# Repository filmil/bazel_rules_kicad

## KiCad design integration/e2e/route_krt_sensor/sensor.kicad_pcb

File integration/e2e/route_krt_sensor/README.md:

<!-- SPDX-License-Identifier: Apache-2.0 -->
# The router comparison on hdlf_example_sensor's board

The board of `//e2e/autoroute` is small: three tracks. This package
compares Freerouting and KiCadRoutingTools on a real one: the placed
board of https://github.com/filmil/hdlf_example_sensor (26 footprints, 22
parts and 4 mounting holes; 18 nets; 10 keep-out zones). It has no copper
pours, so KiCadRoutingTools' exact fill, which runs in KiCad's own
Python, is not exercised here either.

The three files are copies of that repository's build outputs, unchanged,
at commit `0a944e6` (main, 2026-11-23):

`:fixtures_test` checks that the copies still have these sha256s.

| File here | Its target there | sha256 |
|---|---|---|
| `sensor.kicad_pcb` | `//pcb:placed_files` (`placed.kicad_pcb`) | `1300850aa979aa9f9b2683427a06a48fdbad86be9aa11f1fa6b892ab01477736` |
| `sensor.kicad_pro` | `//pcb:placed_files` (`placed.kicad_pro`) | `1ca380c225693be96b08735db7b8e454ca0d44a2888a3865b43e9d0d60b547e8` |
| `sensor.net` | `//elec:netlist` (`netlist.net`) | `52ffbad20848262a8f70201be18e84db21b38a26ba245d2aaf50818048122feb` |

Both routers route under the rules the sensor is made to: JLCPCB's
2-layer 1 oz rules from kicad-druid 1.2.0 (MIT,
`//third_party/kicad_druid`), as hdlf_example_sensor uses them. A first
run under this repository's stricter e2e rules (0.25 mm tracks, 0.2 mm
clearance) was no fair comparison: Freerouting left 9 connections
unrouted, and KiCadRoutingTools narrowed 65 of its 242 segments below
0.25 mm. No 3D models are used.

The routing targets are manual, since routing this board takes minutes;
`:placed`, which only stages the board, and `:fixtures_test` are not, so
CI still analyses the package and checks the copies. Run these in
`integration/` (the integration module), on Linux x86_64 (the only host
KiCadRoutingTools' targets support):

```
bazel test //e2e/route_krt_sensor:freerouting_determinism_test //e2e/route_krt_sensor:krt_determinism_test //e2e/route_krt_sensor:krt_board_determinism_test
bazel build //e2e/route_krt_sensor:comparison
```

(A pattern such as `:all` skips manual targets, so they are named.)

Three routers: Freerouting (`freerouting`), KiCadRoutingTools with its
defaults (`krt`), and KiCadRoutingTools with `--escalation board`
(`krt_board`), which narrows a failing net's tracks only down to the
board's own minimums, not the fab's floor.

`comparison.tsv` has one row per router: the DRC's errors and warnings,
the unconnected items, the track length in mm and the vias
(`//krt:compare`). The routing time is not in it, since it differs between
runs; take it from Bazel's execution log (`--execution_log_json_file`,
the `Freerouting` and `KrtRoute` actions). The results are on issue #104.

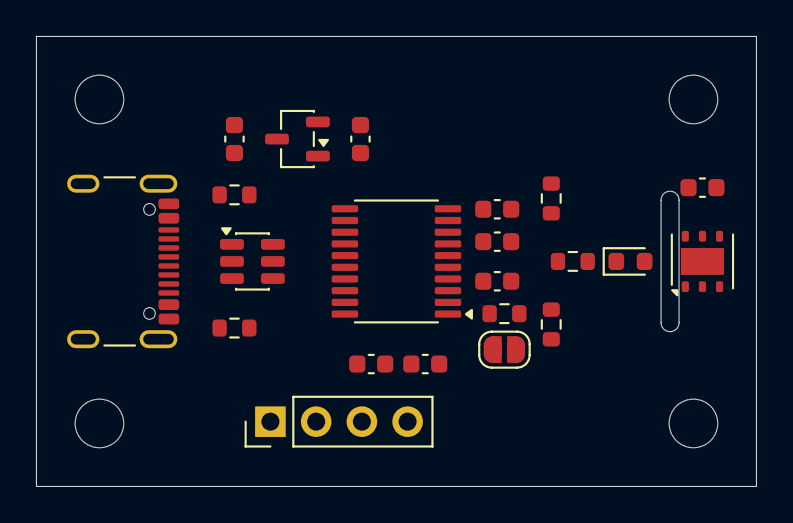
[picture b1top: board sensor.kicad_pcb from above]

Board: 2 copper layers, 40.0 x 25.0 mm, 26 parts (0 on the bottom side), 18 nets, no tracks yet.

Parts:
C1, C2, C6: 1u; C_0603_1608Metric
C3, C7, C8: 100n; C_0603_1608Metric
C4: 4.7u; C_0603_1608Metric
C5: 10n; C_0603_1608Metric
D1: Red; LED_0603_1608Metric
H1, H2, H3, H4: M2.5; MountingHole_2.7mm_M2.5
J1: USB4105-GF-A; USB_C_Receptacle_GCT_USB4105-xx-A_16P_TopMnt_Horizontal
J2: SWD; PinHeader_1x04_P2.54mm_Vertical
JP1: BOOT0; SolderJumper-2_P1.3mm_Open_RoundedPad1.0x1.5mm
R1, R2: 5.1k; R_0603_1608Metric
R3, R4, R5: 10k; R_0603_1608Metric
R6: 1k; R_0603_1608Metric
U1: STM32F042F6P6; TSSOP-20_4.4x6.5mm_P0.65mm
U2: XC6206P332MR; SOT-23-3
U3: HDC2080; Texas_S-PWSON-N6-HDC2080
U4: USBLC6-2SC6; SOT-23-6

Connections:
+3V3: C2.1, C3.1, C4.1, C5.1, C6.1, C8.1, J2.1, JP1.2, R3.2, R4.2, U1.5, U1.16, U2.2, U3.5
BOOT0: JP1.1, R5.1, U1.1
CC1: J1.A5, R1.1
CC2: J1.B5, R2.1
DRDY: U1.6, U3.4
GND: C1.2, C2.2, C3.2, C4.2, C5.2, C6.2, C7.2, C8.2, D1.1, J1.A1, J1.A12, J1.B1, J1.B12, J1.S1, J2.4, R1.2, R2.2, R5.2, U1.15, U2.1, U3.2, U3.3, U4.2
I2C_SCL: R4.1, U1.3, U3.6
I2C_SDA: R3.1, U1.2, U3.1
LED: R6.1, U1.10
LED_A: D1.2, R6.2
NRST: C7.1, U1.4
SWCLK: J2.3, U1.20
SWDIO: J2.2, U1.19
USB_DM: U1.17, U4.6
USB_DM_C: J1.A7, J1.B7, U4.1
USB_DP: U1.18, U4.4
USB_DP_C: J1.A6, J1.B6, U4.3
VBUS: C1.1, J1.A4, J1.A9, J1.B4, J1.B9, U2.3, U4.5
